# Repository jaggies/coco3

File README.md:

# coco3
Some simple applications using the CMOC compiler for the Tandy/Radio Shack TRS Color Computer 3. 

## intray
An ASCII-art ray tracer using fixed-point integer math

## cocoray
Same ray tracer using integer math and coco3's 320x192 mode with 16 colors

## mandel
An ASCII-art Mandelbrot generator

## mandgfx
A Mandelbrot generator using 320x192 graphics mode

## microray
A (more) full-feature ray tracer using floating point (work in progress)

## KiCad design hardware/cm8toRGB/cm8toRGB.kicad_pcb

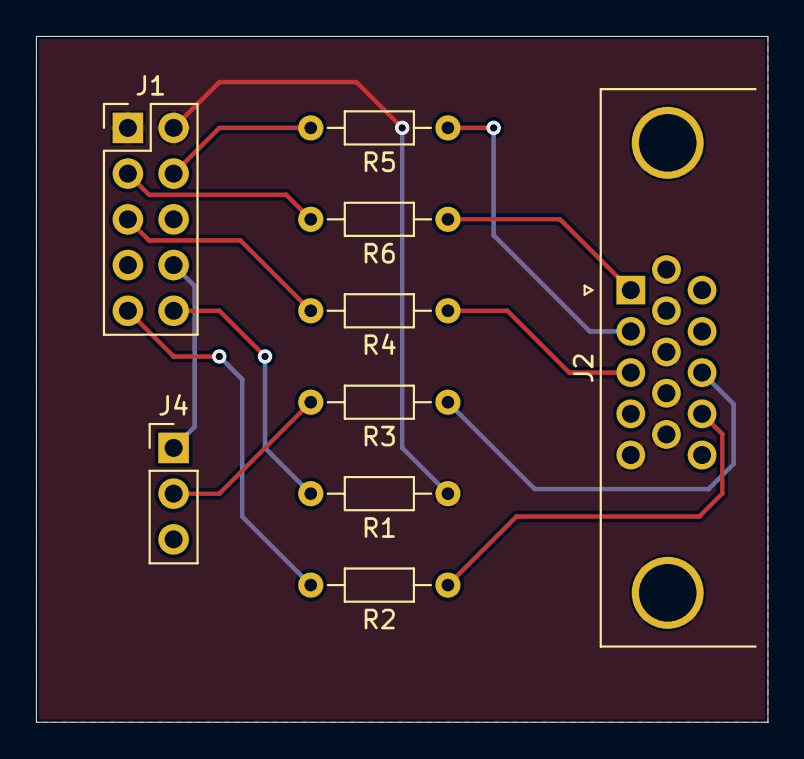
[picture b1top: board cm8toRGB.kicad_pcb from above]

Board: 2 copper layers, 40.6 x 38.1 mm, 9 parts (0 on the bottom side), 13 nets.

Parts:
J1: Conn_02x05_Odd_Even; PinHeader_2x05_P2.54mm_Vertical
J2: VGA; DSUB-15-HD_Female_Horizontal_P2.29x1.98mm_EdgePinOffset3.03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
J4: Conn_01x03; PinHeader_1x03_P2.54mm_Vertical
R1: 0; R_Axial_DIN0204_L3.6mm_D1.6mm_P7.62mm_Horizontal
R2, R3, R4, R5, R6: 75; R_Axial_DIN0204_L3.6mm_D1.6mm_P7.62mm_Horizontal

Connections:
/BLUE: J1.5, R4.2
/GREEN: J1.4, R5.2
/HSYNC: J4.2, R3.2
/RED: J1.3, R6.2
/RGB_SEL: J1.10, R1.2
/VSYNC: J1.9, R2.2
GND: J1.1, J1.2, J2.0, J2.5, J2.6, J2.7, J2.8, J2.9, J2.10, R1.1
unnamed: J1.8, J4.1
unnamed: J2.1, R6.1
unnamed: J2.2, R5.1
unnamed: J2.3, R4.1
unnamed: J2.13, R3.1
unnamed: J2.14, R2.1

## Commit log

2018-03-04 Start CoCo3 projects based on CMOC
2018-03-05 Add microray implementation (WIP)
2018-03-14 Add simple math library with pow() and sqrt()
    - force all CoCo math functions to take float instead of double
    - define simple malloc() and unimplemented free()
    - add stubs for stdio (fopen/close, etc.)
2018-03-14 Add tests for floating point pow() and sqrt()
    Separate disk targets for now
2018-12-09 Add math.h file in attempt to compile ray tracer
2018-12-10 Scaffolding for simple integer-based raytracer
2018-12-10 Enable 6309 native mode
2018-12-10 Add Eclipse files to gitignore
2018-12-10 Move disk targets into build directory
2018-12-10 Always remove disk files when building new disk
2018-12-10 Intersection noisy, but working.
2018-12-10 Temporarily build on host instead of coco.
2018-12-10 Minor tuning for performance and error elimination.
2018-12-10 Cleanup debug info
2018-12-12 Tweaks to get intray to compile/run on host
2018-12-12 Slightly cleaned up version.
    - add rounding to fmult for slightly improved precision
    - simplify toFloat(). better?
    - emulate 16/32 bit on host
2018-12-13 Get working on 6809 again.
2018-12-13 Add shading
2018-12-13 Only calculate fractional multiplier in fsqrt() once.
2018-12-13 Add new "cocoray" graphics display application.
    - Add dithering
    - Reduce precision loss caused by repeatedly adding du,dv
    - Instead, calcuate these as fractional offset from i,j
2018-12-13 Fix bug with camra computation
2018-12-13 Get 640x200 graphics mode working.
2018-12-13 Show the "beam" while raytracing
    (draws a white pixel to show something is going on)
2018-12-20 Fix bug with 32-bit sqrt()
2018-12-20 Addressed several issues with fixed point
    - improved camera fov by adding approximation for tangent.
    - changed methods to be indicative of the source type
    (e.g. fromInt(), fromFloat())
2018-12-20 Only build cocoray on coco target since it does graphics
2018-12-20 Fix overflow conditions for 32-bit math.
2018-12-20 Minor simplifications to fixed library
2018-12-20 Fix regressions on coco3.
2018-12-20 Prepare for refactor
2018-12-20 Refactor and get intray running on OSX.
2018-12-20 Fix missing os library for OSX
2018-12-21 Clean up build target names on OSX.
2018-12-21 Simplify math compatibility library.
2018-12-23 Quick fix for warnings on OSX.
2018-12-23 Add cocoray and mandgfx back to build and fix precisoin issues
    Instead of accumulating errors from adding du/dv, calculate it every time.
2018-12-23 Improve dither routine and fix more precision problems
2018-12-23 Add dependency on libray to intray and cocoray
2018-12-23 Optimize dithering routine for 8 bits.
2018-12-23 Remove duplicate files
2018-12-23 Fix lighting direction
2018-12-24 Add color handling to raytracer
2018-12-29 First pass at adding specular highlights
2018-12-29 Display dithered color on coco3
2018-12-29 New test scene with RGB spheres
2018-12-31 Add background color and fix dark images
    Images were artificially dark due to clamping to 256 before converting
    to uint8_t.
2019-01-03 Add some sample images
2019-01-03 Fix warning about isqrt() on x86
2019-01-19 fpow() performance improvement
2019-01-19 Ignore OSX files
2019-01-27 Add reflection to raytracer.
2019-01-27 Properly handle background color in reflections.
2019-01-27 Fix int8_t type not found on coco.
2019-01-27 Some floating point explorations.
2019-01-27 Add triangle support
2019-01-28 Flip image vertically on CoCo.
2019-01-28 Fix for potential crash if Hit list is uninitialized
2019-01-28 Add experimental directory
2019-02-03 Implement malloc() on CoCo and update testscene to use it.
2019-02-08 First pass at better color rendering
    Just choose nearest color
2019-02-08 Simple error diffusion.
2019-02-08 Slightly better error diffusion.
2019-02-14 Add IRQ-based palette test
2019-02-14 Reset palette index on vertical sync
2019-02-17 Experiment with dynamic palette control per line.
    Now with assembly!
2019-02-18 Switch to using FIRQ for hsync and IRQ for vsync.
2019-02-19 Start new cc3 library with hw and gfx routines
2019-02-19 Add field sequential test
2019-02-20 Move some more stuff into graphics library.
2019-02-20 Remember to clear the damn IRQs
    The emulator seems to just look for an edge. As a consequence,
    the real-world CoCo gets into an infinite loop in the ISR. Oops.
2019-02-20 Fixup: port mandgfx to cc3gfx libs
2019-02-21 Sync looks correct on scope, but still corrupts graphics
    IRQ -> 60Hz
    FIRQ -> 15750Hz
2019-02-21 Only clear the necessary FIRQ flags and ensure PIA IRQ is disabled.
    With this change, the IRQ line is quiet and the FIRQ line is running
    at 60Hz.
2019-02-21 Disable historic PIA IRQs
    With this change, IRQ/FIRQ pins are properly running at 60Hz/15750Hz,
    respectively. But graphics is still corrupt. Hmm.
2019-02-25 Add new graphics commands: setPixel(), setMode() and clear()
2019-02-25 Use memset() for better clear performance
2019-02-25 Properly handle bit depths and slight performance optimization.
2019-02-26 Replace static references with constants in hwgfx.h
2019-02-26 Use function pointer to avoid runtime decisions in setPixel()
2019-02-26 Minor optimization
2019-02-26 Get rid of calls to dword operations for memset1.
2019-02-27 Add memcpy24 to hardware routines.
2019-02-27 Add new pixel copy routines to render quick spans.
2019-02-27 Use new span routines and optimize per-line palette to allow up to 4 swaps
2019-02-28 Fix bug with memcpy24.
2019-02-28 Modify field to use new graphics library commands
2019-02-28 Add simpler, faster dithering routine
2019-02-28 Allow the program to specify where to draw and display graphics from.
2019-02-28 New Field Sequential mode with RGB interpolated field
2019-02-28 Enable vertical IRQ while drawing.
2019-02-28 Start showing field sequential IRQ when drawing starts
2019-03-01 Get field program working on coco3
    Before this, IRQ line was being held low indefinitely.
2019-03-02 Enable full 16 pallete swap during hblank (6309 only!)
2019-03-02 Clean up cocoray and move functions to cc3util.c
2019-03-02 Rename dith6x2 to dither6x2.
2019-03-02 Switch to single ISR routine and monitor FIRQEN bits instead
2019-03-02 Use "ultra high res" mode to show maximum color selection
2019-03-02 Add fast memset assembly code using 6309 TFM instrution
2019-03-02 Move some stuff around
2019-03-03 Convert cocoray to use new cc3 graphics library
2019-03-03 Add fastmult() using MULD instruction.
2019-03-31 Add lines and rectangles to graphics library
2019-03-31 Eliminate warnings in float.c
2019-03-31 Minor cleanup in cc3gfx.c
2019-03-31 Remove global 'mask' constant.
2019-03-31 Simplify line drawing function.
2019-03-31 Move dither into cc3 since it's called by cc3 routines.
2019-03-31 Cleanup cc3gfx
    - Add GfxState
    - More documentation
    - Remove ECB graphics mode declarations
2019-03-31 Update mandgfx to use cc3gfx.
    It's broken now. Not sure what happened.
2019-03-31 Port integer mandelbrot to fixed.
2019-03-31 Fix x86 build for some targets
2019-03-31 Add workaround for broken MULD instruction on most emulators :(
2019-03-31 Remove unused 'fract' declaration.
2019-04-01 Simplify cc3hw and cc3gfx
2019-04-01 Use more robust palette in lines.c
2019-04-03 Add ngon demo and sin/cos math routines.
2019-04-03 Add high performance relative raster operations.
    Replaces expensive per-pixel 16-bit multiply with per-pixel addition.
2019-04-03 Compute mask on the fly. Faster?
2019-04-06 Precompute base page for ~2x performance improvement.
2019-04-06 Remove redundant calculation.
2019-04-07 Document and enforce page boundary limits.
2019-04-07 Inline rasterInc/Dec methods for about 7% speedup
2019-04-07 inline set method for about 12% speed improvement.
2019-04-07 Move page preserving code outside loop. ngon runs in 68.2s
2019-04-07 Add basic circle drawing.
2019-04-07 Test case with both random and increasing circles
    Built-in random number generator is crap, so mix up the bits a little.
2019-04-07 Use midpoint algorithm to draw cleaner (more round) circles.
2019-04-12 Add triangle rasterizer from college.
2019-04-13 Fix bug with fillPixels
2019-04-13 Use fillPixels() instead of setPixel()
2019-04-14 Use Bresenham's to render triangle edges.
2019-04-14 Add better test cases and make bug fixes (almost there)
2019-04-14 Fix remaining bugs with triangle rasterization.
    Due to known C optimization with &&, the second call
    to walkEdge() was being ignored.
2019-04-14 Workaround for cracks in long, skinny, multi-part triangles.
    Sometimes the Y component doesn't line up for upper / lower halves
    of triangles. Until that's fixed, this seems reasonable.
2019-04-14 Eliminate array access from internal triangle structure.
2019-04-14 Document and minor clean up of cc3raster
2019-04-15 Make triangle test finite and add larger triangles
2019-04-15 Get rid of color parameter in more API.
2019-04-15 More code refactoring; get rid of more color parameters.
2019-04-15 Optimize triangle rendering to eliminate calls to min() and abs()
    Always render left-to-right and ensure that fillPixels can handle
    minor errors (negative numbers) w/o barfing too much.
2019-04-16 Enable filled circles
2019-04-16 Fix some TODOs
2019-04-21 Add TODO list
2019-04-21 Clean up triangle demo
2019-04-21 Faster triangle rendering
    Avoid extran 32-bit copy in cc3gfx by removing local variable.
    Avoid extra multiplies setting end pixels by using new rasterSpan() function
    Better handling of split spans.
2019-04-21 Minor fix to span accounting and Remove unused code
2019-04-21 Remove references to fillPixels()
    Deprecated; use rasterSpan() instead
2019-04-21 Minor cleanup.
2019-04-21 Remove fillPixels() routine and switch to using new raster routines.
2019-04-21 Add random rectangle rendering after test pattern.
2019-04-21 Slightly more efficient rect() code.
2019-04-21 Minor performance improvements for circle.
2019-04-21 Allow leftward spans.
2019-04-21 Use full resolution for triangles.c
2019-04-23 Slightly faster line rendering by pre-calculating -dy
2019-04-23 Always render lines in positive Y direction to agree with triangle rendering
    Benchmark ngon: 66.9s
2019-04-23 Add qix-like demo using lines and palette manipulation for speed.
2019-04-24 Much faster version by rotating palette and drawing only the head/tail.
2019-04-24 Use modulo arithmetic instead of shifting values
2019-04-24 Use constants for page-related stuff. Confirmed cmoc generates the same code
2019-04-24 Minor cleanup in field.c
2019-04-24 Move page window to 0x8000 from 0xC000 in prep for faster lines
2019-04-27 Add Matrix math.
2019-04-27 Start cube demo.
2019-04-27 Optimize cube demo
    - hidden surface removal by finding closest vertex an rendering only
    faces attached to it.
    - optimize matrix math
2019-04-27 Fix cracks in triangles
2019-04-28 Add wireframe mode to cube demo.
2019-04-28 Eliminate unused conditional.
2019-04-28 Simplify edge walking code in triangle code
2019-04-28 Cleanup matrix code.
2019-04-28 Add fixed point matrix code (untested)
2019-04-28 Change RotationMatrixVector name to be consistent with fixed point version.
2019-10-30 Add efficient wireframe mode to cube drawing.
2019-11-02 Optimize performance by moving matrix math outside loop.
2019-11-02 Pause at frame boundary for smoother graphics.
2019-11-02 Apply mask improvement patches
2019-11-02 Don't depend on coco.h to allow this to compile on PC.
2019-11-04 Enable solid cube by default.
2019-11-06 Add sin(x)/x demo app.
2019-11-06 Add HD6309 build variant
2019-11-06 Rename imatrix to fmatrix
2019-11-06 Factor out fixed point into separate linkable library
2020-05-25 Switch to dynamic allocation instead of static allocation.
    Also turn on code optimization and static stack protection flag.
2020-05-25 Add matrix math routines (untested)
2020-09-12 Add basic instruction documentation.
2021-10-10 Add CM8 RGB cable schematic
